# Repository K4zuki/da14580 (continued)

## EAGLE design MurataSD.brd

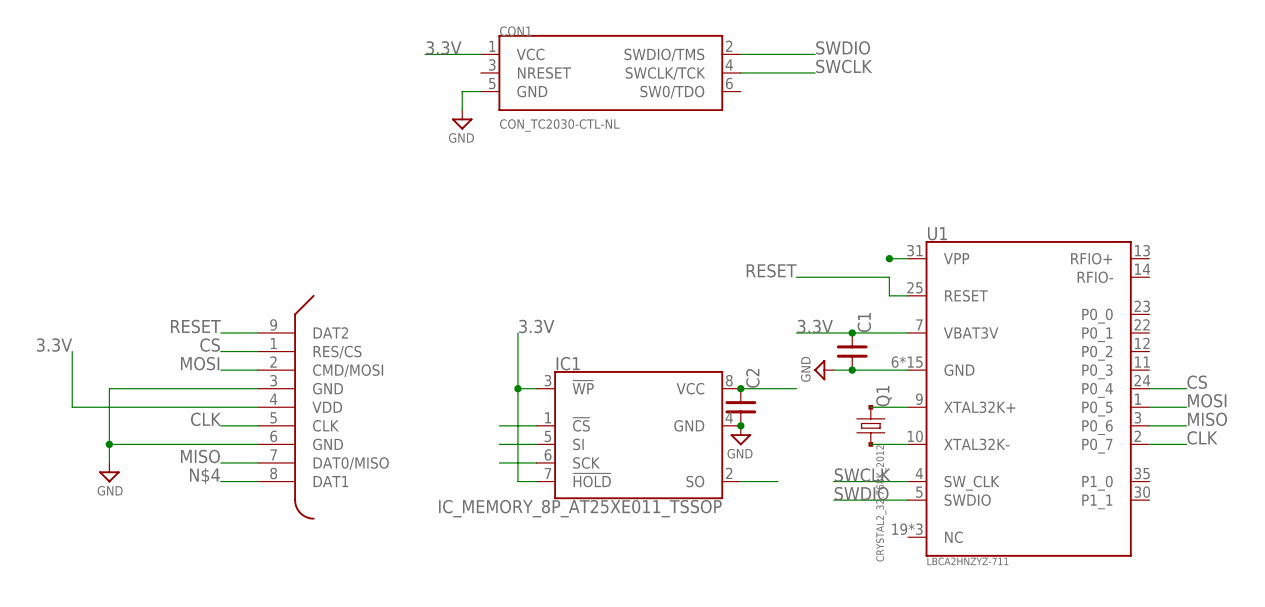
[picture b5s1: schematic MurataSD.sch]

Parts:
C1, C2: C_SMD_0.1U_1005; C0402
CON1: CON_TC2030-CTL-NL; CON_TC2030-IDC-NL
IC1: IC_MEMORY_8P_AT25XE011_TSSOP; IC_08_0.65_160MIL
Q1: CRYSTAL2_32.768K_2012; CR_2125
U1: LBCA2HNZYZ-711; IC_MURATA_LBCA2HNZYZ-711
U2: BOARD_MMC

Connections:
3.3V: C1.1, C2.1, CON1.1 (VCC), IC1.3 (!WP), IC1.7 (!HOLD), IC1.8 (VCC), U1.7 (VBAT3V), U2.4 (VDD)
CLK: IC1.6 (SCK), U1.2 (P0_7), U2.5 (CLK)
CS: IC1.1 (!CS), U1.24 (P0_4), U2.1 (RES/CS)
GND: C1.2, C2.2, CON1.5 (GND), IC1.4 (GND), U1.6 (GND), U1.8 (GND), U1.15 (GND), U1.16 (GND), U1.17 (GND), U1.18 (GND), U1.20 (GND), U1.21 (GND), U1.26 (GND), U1.27 (GND), U1.28 (GND), U1.29 (GND), U1.32 (GND), U1.33 (GND), U1.34 (GND), U2.3 (GND), U2.6 (GND)
MISO: IC1.2 (SO), U1.3 (P0_6), U2.7 (DAT0/MISO)
MOSI: IC1.5 (SI), U1.1 (P0_5), U2.2 (CMD/MOSI)
unnamed: Q1.1, U1.9 (XTAL32K+)
unnamed: Q1.2, U1.10 (XTAL32K-)
RESET: U1.25 (RESET), U2.9 (DAT2)
SWCLK: CON1.4 (SWCLK/TCK), U1.4 (SW_CLK)
SWDIO: CON1.2 (SWDIO/TMS), U1.5 (SWDIO)

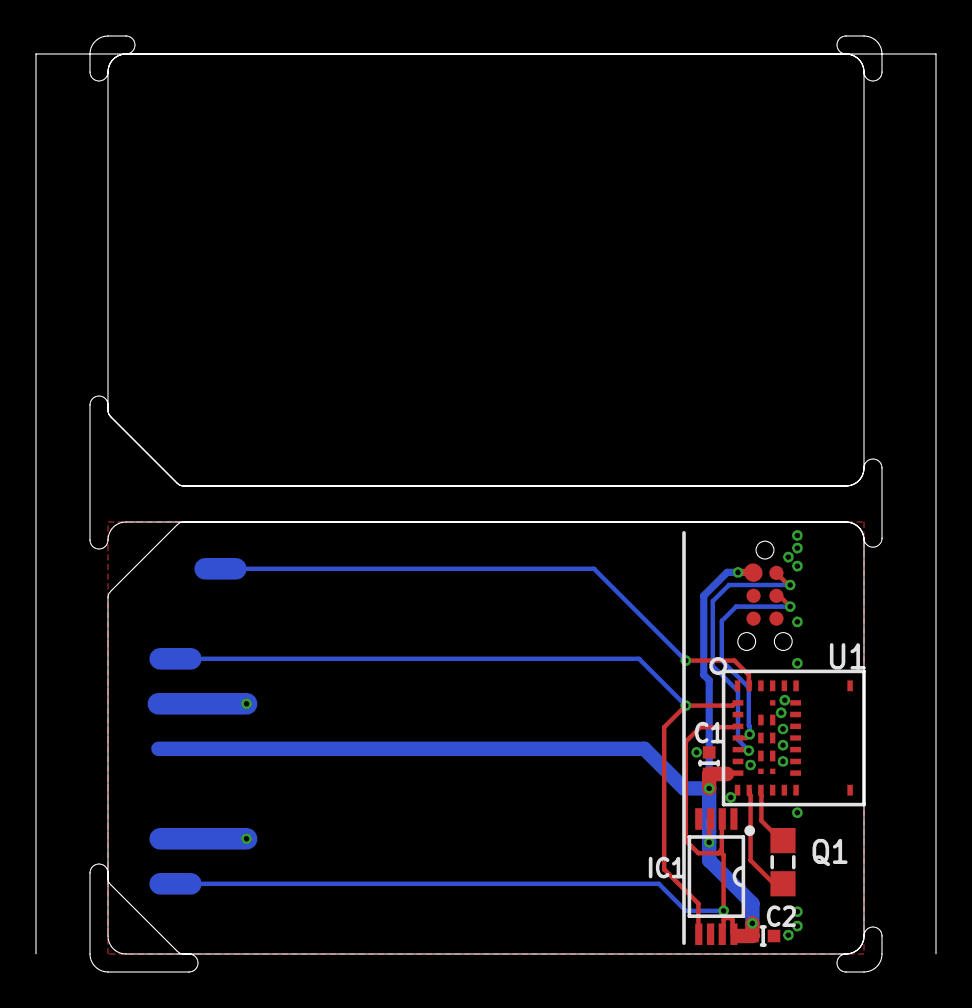
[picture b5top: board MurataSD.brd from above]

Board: 2 copper layers, 44.0 x 52.0 mm, 7 parts (0 on the bottom side), 11 nets.

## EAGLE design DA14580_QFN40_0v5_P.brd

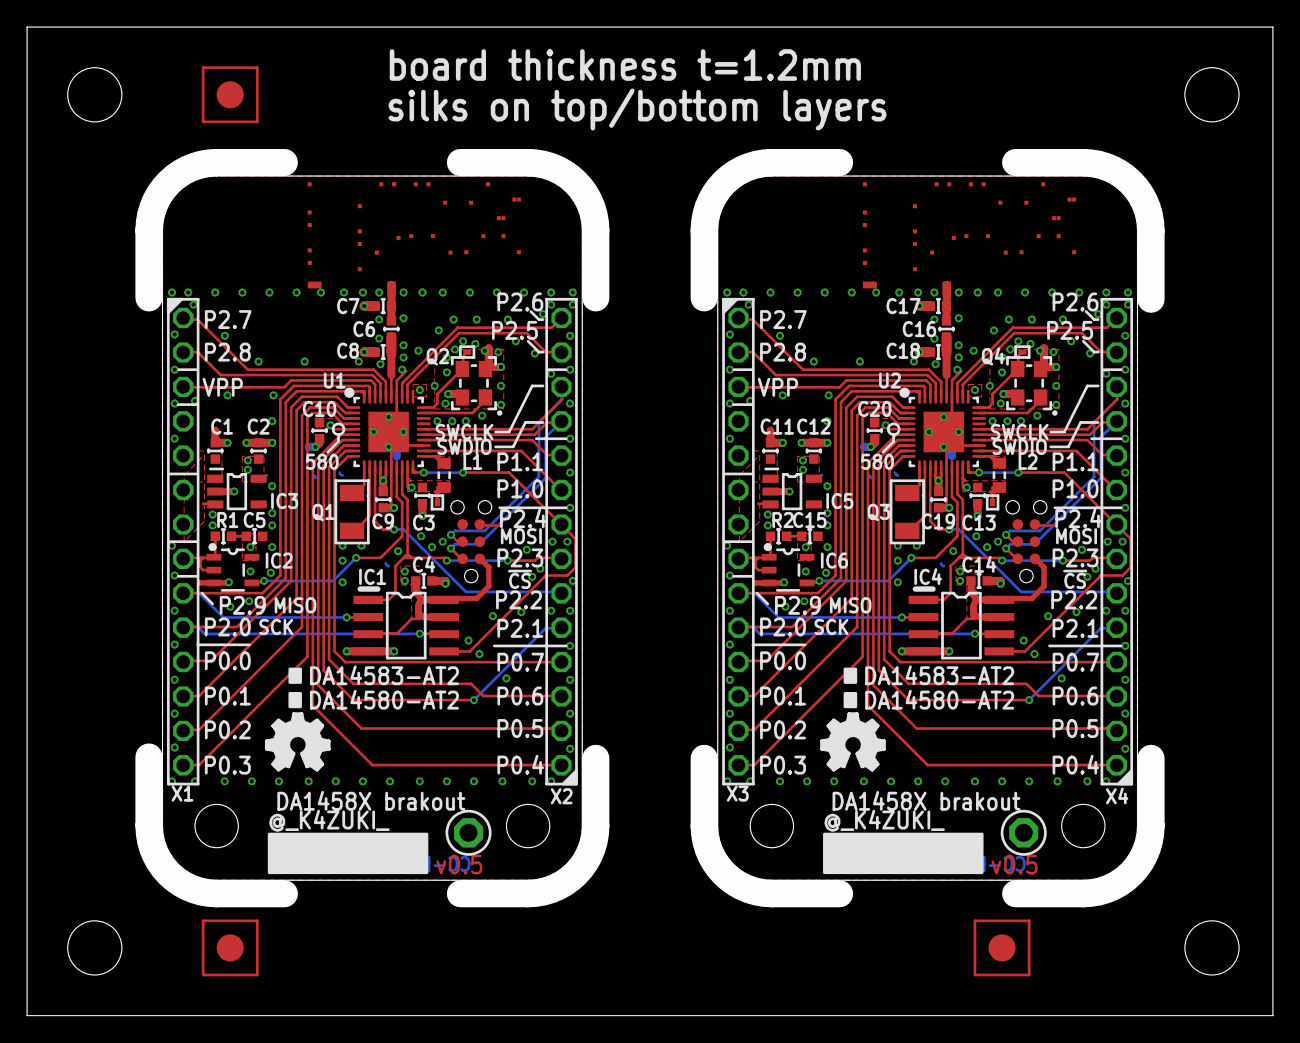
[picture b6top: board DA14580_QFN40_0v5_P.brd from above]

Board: 2 copper layers, 92.0 x 73.0 mm, 55 parts (0 on the bottom side), 70 nets.

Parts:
C1, C2, C3, C4, C5, C9, C10, C11, C12, C13, C14, C15, C19, C20: C0402
C6, C7, C8, C16, C17, C18: NM; C0402
CON1, CON2: CON_TC2030-CTL-NL; CON_TC2030-IDC-NL
IC1, IC4: IC_MEMORY_8P_AT25XE011_SOP; IC_08_1.27_150MIL
IC2, IC6: NC7SZ00M5XCT-ND; SOT23-5
IC3, IC5: LDO5_3.3_SOT23; IC_05_0.95_50MIL
L1, L2: L_1608
Q1, Q3: 32.768k; CRYSTAL_FC-135
Q2, Q4: 16M/2520; CLOCK_2520
R1, R2: C0402
TP1, TP2, TP5, TP6: TESTPAD; TP06RECT
TP3, TP4: TPPAD1-13; P1-13
TP91, TP92, TP93: TESTPAD_F; FIDUCIAL
U1, U2: DA14583AT2; QFN40_0.4P5.0X5.0
U$1, U$3: ANT_IFA; ANT_IFA_V2
U$2, U$4: ICON_OSHW
X1, X2, X3, X4: SSW-114-02-S-S

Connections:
!RESET!: IC2.1, IC2.2, R1.1, X1.8
!RESET!1: IC6.1, IC6.2, R2.1, X3.8
GND: C1.2, C2.2, C3.2, C4.2, C5.2, C6.2, C7.1, C7.2, C8.2, C9.2, C10.2, CON1.5, IC1.4, IC2.3, IC3.2, Q2.2, Q2.4, TP3.TP, U1.16, U1.23, U1.34, U1.BP, U$1.ANT, U$1.GND, U$1.GND@1, U$1.GND@2, U$1.GND@3, U$1.GND@4, U$1.GND@5, U$1.GND@6, U$1.GND@7, U$1.GND@8, U$1.GND@9, U$1.GND@10, U$1.GND@11, U$1.GND@12, U$1.GND@13, U$1.GND@14, U$1.GND@15, U$1.GND@16, U$1.GND@17, U$1.GND@18, U$1.GND@19, U$1.GND@20, U$1.GND@21, U$1.GND@22, U$1.GND@23, U$1.GND@24, U$1.GND@25, U$1.GND@26, U$1.GND@27, U$1.GND@28, U$1.GND@29, U$1.GND@30, X1.4, X1.5
GND1: C11.2, C12.2, C13.2, C14.2, C15.2, C16.2, C17.1, C17.2, C18.2, C19.2, C20.2, CON2.5, IC4.4, IC5.2, IC6.3, Q4.2, Q4.4, TP4.TP, U2.16, U2.23, U2.34, U2.BP, U$3.ANT, U$3.GND, U$3.GND@1, U$3.GND@2, U$3.GND@3, U$3.GND@4, U$3.GND@5, U$3.GND@6, U$3.GND@7, U$3.GND@8, U$3.GND@9, U$3.GND@10, U$3.GND@11, U$3.GND@12, U$3.GND@13, U$3.GND@14, U$3.GND@15, U$3.GND@16, U$3.GND@17, U$3.GND@18, U$3.GND@19, U$3.GND@20, U$3.GND@21, U$3.GND@22, U$3.GND@23, U$3.GND@24, U$3.GND@25, U$3.GND@26, U$3.GND@27, U$3.GND@28, U$3.GND@29, U$3.GND@30, X3.4, X3.5
unnamed: C6.1, C8.1, U1.35
unnamed: Q3.1, U2.12
unnamed: Q3.2, U2.11
unnamed: Q4.1, U2.29
unnamed: Q4.3, TP6.TP, U2.30
unnamed: L1.2, U1.21
unnamed: L2.2, U2.21
unnamed: C13.1, L2.1, TP5.TP, U2.19, U2.31
unnamed: C3.1, L1.1, TP1.TP, U1.19, U1.31
unnamed: C16.1, C18.1, U2.35
unnamed: Q1.1, U1.12
unnamed: Q1.2, U1.11
unnamed: Q2.1, U1.29
unnamed: Q2.3, TP2.TP, U1.30
P0_0: U1.1, X1.11
P0_1: U1.2, X1.12
P0_2: U1.3, X1.13
P0_3: U1.4, X1.14
P0_4: U1.6, X2.1
P0_5: U1.7, X2.2
P0_6: U1.9, X2.3
P0_7: U1.10, X2.4
P0_8: U2.1, X3.11
P0_9: U2.2, X3.12
P0_10: U2.3, X3.13
P0_11: U2.4, X3.14
P0_12: U2.7, X4.2
P0_13: U2.6, X4.1
P0_14: U2.10, X4.4
P0_15: U2.9, X4.3
P1_0: U1.22, X2.9
P1_1: U1.24, X2.10
P1_4: U2.22, X4.9
P1_5: U2.24, X4.10
P2_0: IC1.6, U1.40, X1.10
P2_1: U1.8, X2.5
P2_2: U1.13, X2.6
P2_3: IC1.1, U1.18, X2.7
P2_4: IC1.5, U1.20, X2.8
P2_5: U1.32, X2.13
P2_6: U1.33, X2.14
P2_7: U1.36, X1.1
P2_8: U1.37, X1.2
P2_9: IC1.2, U1.39, X1.9
P2_10: IC4.1, U2.18, X4.7
P2_11: U2.13, X4.6
P2_12: IC4.6, U2.40, X3.10
P2_13: U2.8, X4.5
P2_14: U2.32, X4.13
P2_15: U2.33, X4.14
P2_16: IC4.2, U2.39, X3.9
P2_17: IC4.5, U2.20, X4.8
P2_18: U2.36, X3.1
P2_19: U2.37, X3.2
RESET: IC2.4, U1.17
RESET1: IC6.4, U2.17
SWCLK: CON1.4, U1.26, X2.12
SWCLK1: CON2.4, U2.26, X4.12
SWDIO: CON1.2, U1.25, X2.11
SWDIO1: CON2.2, U2.25, X4.11
VCC: C2.1, C4.1, C5.1, C9.1, C10.1, CON1.1, IC1.3, IC1.7, IC1.8, IC2.5, IC3.5, R1.2, U1.5, U1.14, U1.15
VCC1: C12.1, C14.1, C15.1, C19.1, C20.1, CON2.1, IC4.3, IC4.7, IC4.8, IC5.5, IC6.5, R2.2, U2.5, U2.14, U2.15
VDD: C1.1, IC3.1, IC3.3, X1.6, X1.7
VDD1: C11.1, IC5.1, IC5.3, X3.6, X3.7
VPP: U1.38, X1.3
VPP1: U2.38, X3.3

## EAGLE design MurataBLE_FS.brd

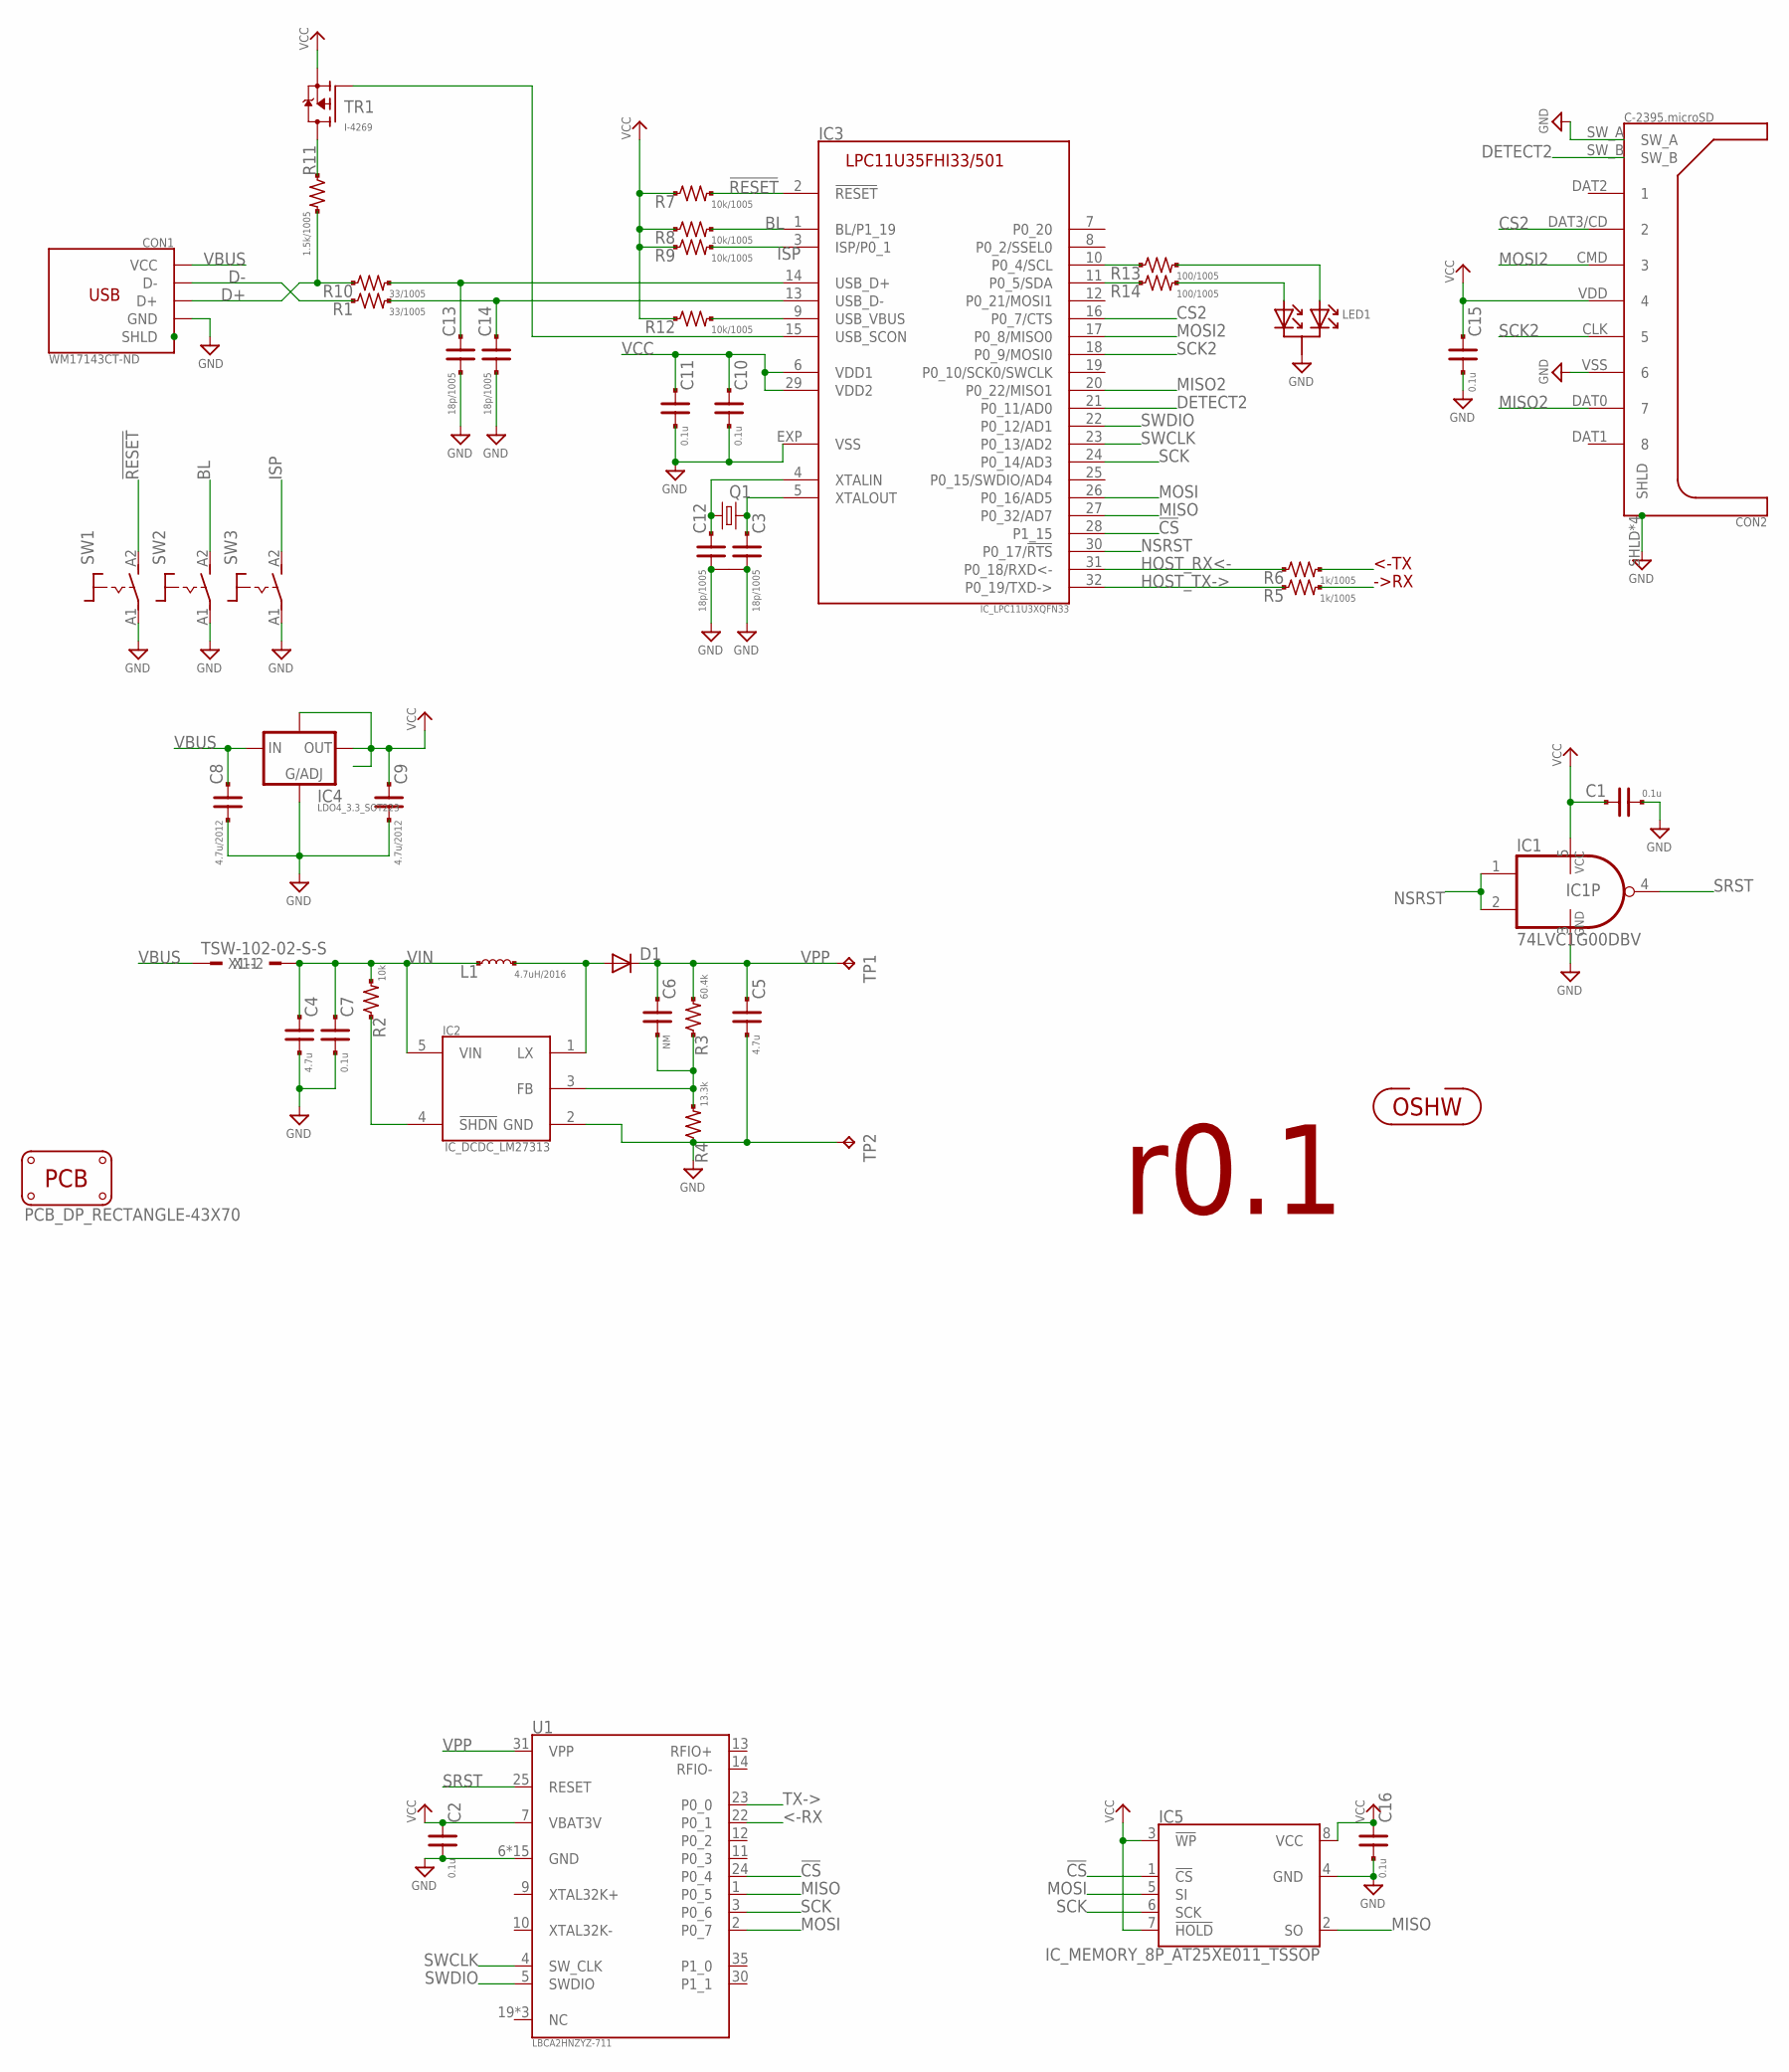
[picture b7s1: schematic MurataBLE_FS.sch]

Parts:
C1, C2, C10, C11, C16: 0.1u; C0402
C3, C12, C13, C14: 18p/1005; C0402
C4, C5: 4.7u; CR_2125
C6: NM; CR_1608
C7, C15: 0.1u; CR_1608
C8, C9: 4.7u/2012; CR_2125
CON1: WM17143CT-ND; CON_USB_47589-0001MOLEX
CON2: C-2395.microSD; CON_MICROSD_C2395
D1: DIODE_SMALL; DIODE_2125
IC1: 74LVC1G00DBV; SOT23-5
IC2: IC_DCDC_LM27313; IC_05_0.95_50MIL
IC3: IC_LPC11U3XQFN33; HVQFN33
IC4: LDO4_3.3_SOT223; IC_SOT223
IC5: IC_MEMORY_8P_AT25XE011_TSSOP; IC_08_0.65_160MIL
L1: 4.7uH/2016; L_2016
LED1: LED_1SEG_A2K1; SOT95P300X140-3N
PCB1: PCB_DP_RECTANGLE-43X70; DP7043_V1
Q1: CRYSTAL4_12M_3225; CLOCK_3225
R1, R10: 33/1005; C0402
R2: 10k; R_1608_PADPAD
R3: 60.4k; R_1608_PADPAD
R4: 13.3k; R_1608_PADPAD
R5, R6: 1k/1005; C0402
R7, R8, R9, R12: 10k/1005; C0402
R11: 1.5k/1005; C0402
R13, R14: 100/1005; C0402
SW1, SW3: TACTSW2_BK_P807X; SW_TACTSW_P8073
SW2: TACTSW2_WH_P807X; SW_TACTSW_P8073
TP1: P7592; P1-13
TP2: P7591; P1-13
TR1: I-4269; SOT95P300X140-3N
U1: LBCA2HNZYZ-711; IC_MURATA_LBCA2HNZYZ-711
U$1: ICON_OSHW
X1: TSW-102-02-S-S

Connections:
!CS!: IC3.28 (P1_15), IC5.1 (!CS), U1.24 (P0_4)
!RESET!: IC3.2 (!RESET!), R7.2, SW1.A2 (S)
<-RX: R5.2, U1.22 (P0_1)
BL: IC3.1 (BL/P1_19), R8.2, SW2.A2 (S)
CS2: CON2.DAT3/CD (2), IC3.16 (P0_7/CTS)
D+: CON1.3 (D+), R10.1, R11.2
D-: CON1.2 (D-), R1.1
DETECT2: CON2.SW_B, IC3.21 (P0_11/AD0)
GND: C1.2, C2.2, C3.2, C4.2, C5.2, C7.2, C8.2, C9.2, C10.2, C11.2, C12.2, C13.2, C14.2, C15.2, C16.2, CON1.5 (GND), CON2.SHLD, CON2.SHLD@2 (SHLD), CON2.SHLD@3 (SHLD), CON2.SHLD@4 (SHLD), CON2.SW_A, CON2.VSS (6), IC1.3 (GND), IC2.2 (GND), IC3.EXP (VSS), IC4.1 (ADJ), IC5.4 (GND), LED1.3 (K1), Q1.2, Q1.4, R4.1, SW1.A1, SW2.A1, SW3.A1, TP2.TP, U1.6 (GND), U1.8 (GND), U1.15 (GND), U1.16 (GND), U1.17 (GND), U1.18 (GND), U1.20 (GND), U1.21 (GND), U1.26 (GND), U1.27 (GND), U1.28 (GND), U1.29 (GND), U1.32 (GND), U1.33 (GND), U1.34 (GND)
HOST_RX<-: IC3.31 (P0_18/RXD<-), R6.1
HOST_TX->: IC3.32 (P0_19/TXD->), R5.1
ISP: IC3.3 (ISP/P0_1), R9.2, SW3.A2 (S)
MISO: IC3.27 (P0_32/AD7), IC5.2 (SO), U1.1 (P0_5)
MISO2: CON2.DAT0 (7), IC3.20 (P0_22/MISO1)
MOSI: IC3.26 (P0_16/AD5), IC5.5 (SI), U1.2 (P0_7)
MOSI2: CON2.CMD (3), IC3.17 (P0_8/MISO0)
unnamed: R11.1, TR1.3 (D)
unnamed: IC3.10 (P0_4/SCL), R13.1
unnamed: CON1.SHD (SHLD), CON1.SHD$1 (SHLD), CON1.SHD$2 (SHLD), CON1.SHD$3 (SHLD), CON1.SHD$4 (SHLD), CON1.SHD$5 (SHLD), CON1.SHD$6 (SHLD), CON1.SHD$7 (SHLD)
unnamed: C12.1, IC3.4 (XTALIN), Q1.1
unnamed: IC3.11 (P0_5/SDA), R14.1
unnamed: D1.A, IC2.1 (LX), L1.2
unnamed: IC2.4 (!SHDN!), R2.1
unnamed: LED1.2 (A2), R13.2
unnamed: C6.2, IC2.3 (FB), R3.1, R4.2
unnamed: C3.1, IC3.5 (XTALOUT), Q1.3 (2)
unnamed: IC3.15 (USB_SCON), TR1.1 (G)
unnamed: IC3.9 (USB_VBUS), R12.2
unnamed: LED1.1 (A1), R14.2
unnamed: C13.1, IC3.14 (USB_D+), R10.2
unnamed: C14.1, IC3.13 (USB_D-), R1.2
NSRST: IC1.1 (I0), IC1.2 (I1), IC3.30 (P0_17/!RTS!)
SCK: IC3.24 (P0_14/AD3), IC5.6 (SCK), U1.3 (P0_6)
SCK2: CON2.CLK (5), IC3.18 (P0_9/MOSI0)
SRST: IC1.4 (O), U1.25 (RESET)
SWCLK: IC3.23 (P0_13/AD2), U1.4 (SW_CLK)
SWDIO: IC3.22 (P0_12/AD1), U1.5 (SWDIO)
TX->: R6.2, U1.23 (P0_0)
VBUS: C8.1, CON1.1 (VCC), IC4.3 (IN), X1.1
VCC: C1.1, C2.1, C9.1, C10.1, C11.1, C15.1, C16.1, CON2.VDD (4), IC1.5 (VCC), IC3.6 (VDD1), IC3.29 (VDD2), IC4.2 (OUT), IC4.4 (OUT/EN/NC), IC5.3 (!WP), IC5.7 (!HOLD), IC5.8 (VCC), R7.1, R8.1, R9.1, R12.1, TR1.2 (S), U1.7 (VBAT3V)
VIN: C4.1, C7.1, IC2.5 (VIN), L1.1, R2.2, X1.2
VPP: C5.1, C6.1, D1.K (C), R3.2, TP1.TP, U1.31 (VPP)

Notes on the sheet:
r0.1
->RX
<-TX

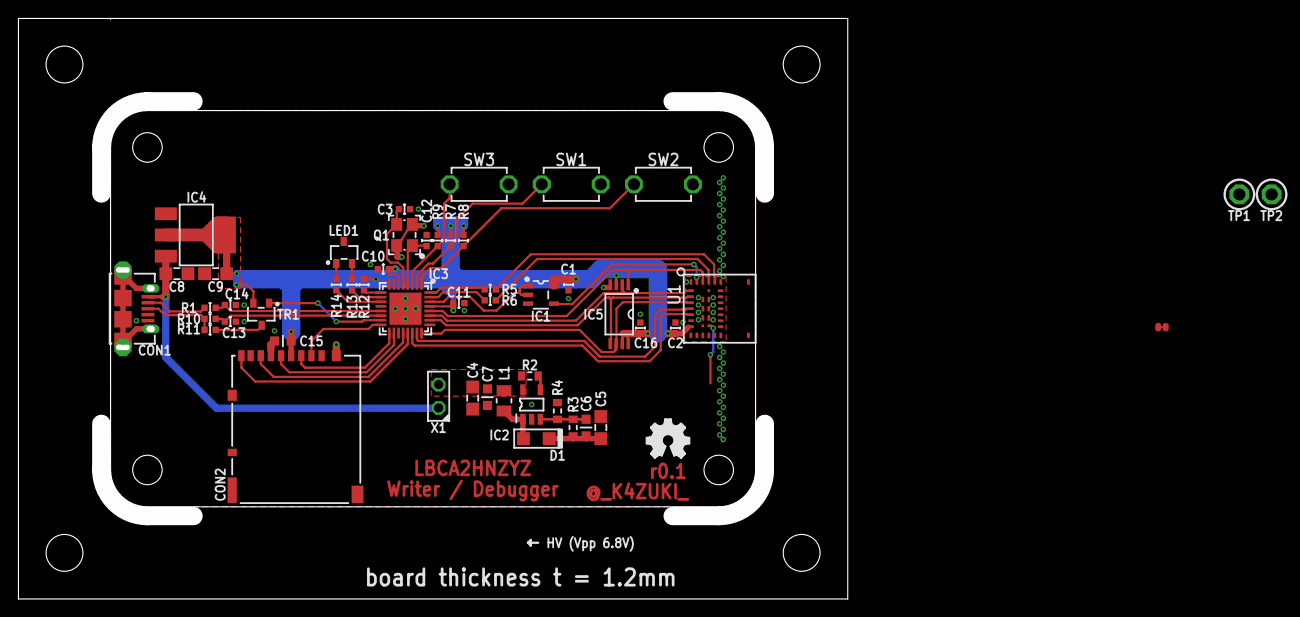
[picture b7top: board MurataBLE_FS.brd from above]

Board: 2 copper layers, 90.0 x 63.0 mm, 51 parts (0 on the bottom side), 42 nets.

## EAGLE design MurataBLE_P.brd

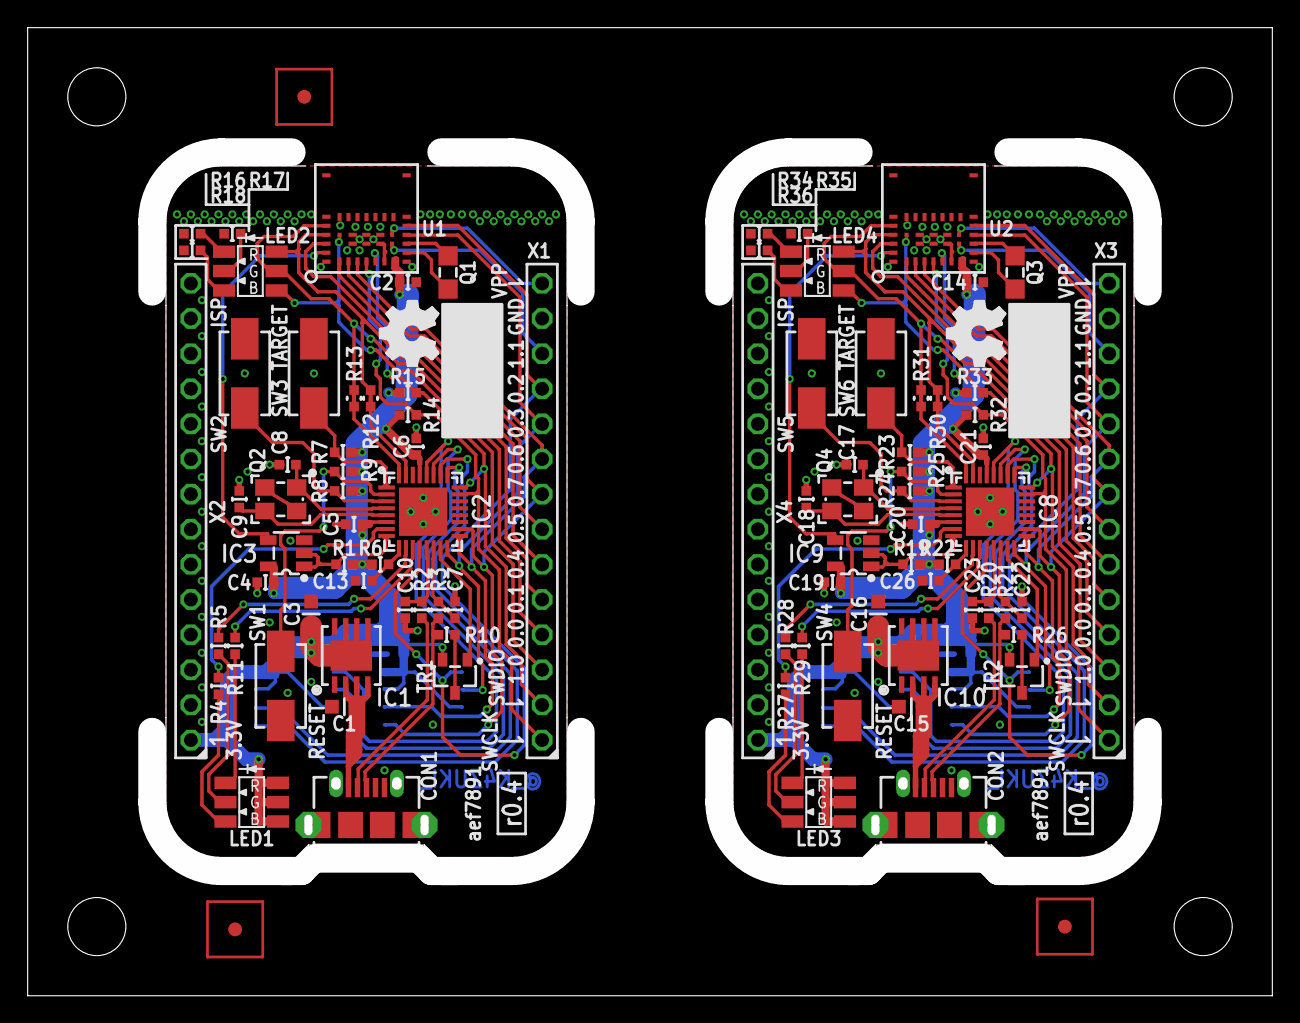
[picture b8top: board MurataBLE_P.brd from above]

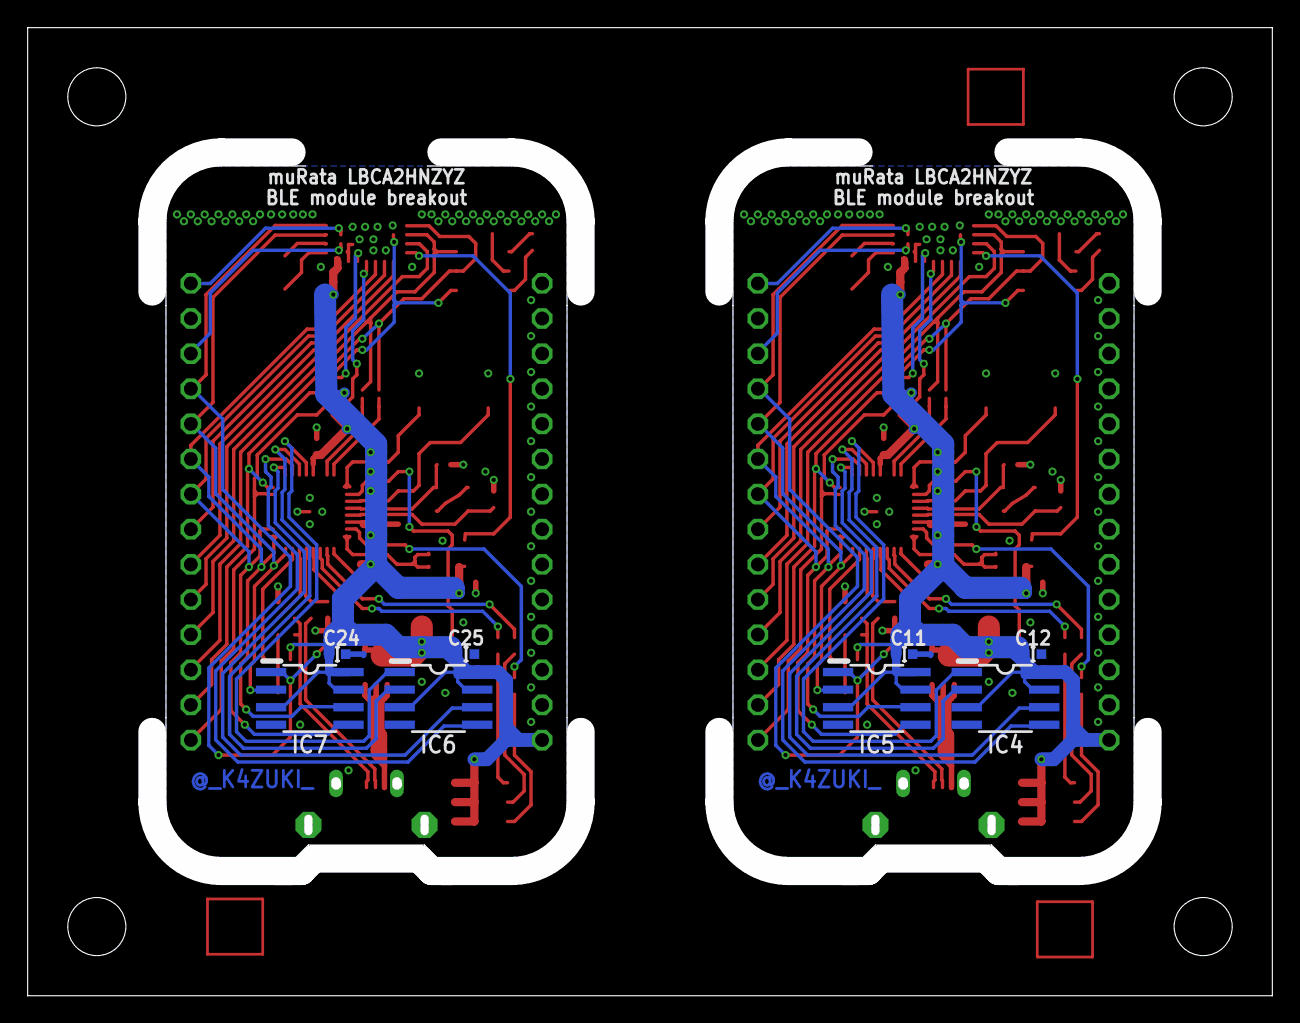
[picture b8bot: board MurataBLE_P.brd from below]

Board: 2 copper layers, 90.0 x 70.0 mm, 113 parts (8 on the bottom side), 94 nets.

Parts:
C1, C3, C15, C16: 1u/1608; CR_1608
C2, C4, C5, C6, C11, C12, C13, C14, C19, C20, C21, C24, C25, C26: 0.1u/1005; C0402
C7, C8, C9, C10, C17, C18, C22, C23: 18p/1005; C0402
CON1, CON2: 47589-0001; CON_USB_47589-0001MOLEX
GIT1, GIT2: aef7891; GIT-REVISION
IC1, IC10: DFN80P410X410_8N
IC2, IC8: LPC11U35_QFN33; HVQFN33
IC3, IC9: NC7SZ00; SOT95P280X145-5N
IC4, IC6: AT25DN512C; IC_08_1.27_150MIL
IC5, IC7: AT25XE011; IC_08_1.27_150MIL
ICON1, ICON3: r0.4; ICON_REVISION1.2
ICON2, ICON4: NC; ICON_OSHW
LED1, LED2, LED3, LED4: LED_3SEG; LED_3SEG_SMD
P1, P2, P3, P4, P5, P6, P7, P8: NC; PCB_CORNER_NH
Q1, Q3: 32.768K/2012; CR_2125
Q2, Q4: 12M/3225; CLOCK_3225
R1, R6, R7, R8, R9, R14, R15, R19, R22, R23, R24, R25, R32, R33: 10k/1005; C0402
R2, R3, R20, R21: 33/1005; C0402
R4, R5, R11, R16, R17, R18, R27, R28, R29, R34, R35, R36: 1k/1005; C0402
R10, R26: 1.5k/1005; C0402
R12, R13, R30, R31: NC; R0402SHORT
SW1, SW2, SW3, SW4, SW5, SW6: FSM2JMTR; SW_TACTSW_FSM2JMTR
TP100, TP101, TP102: NC; FIDUCIAL
TR1, TR2: BSS84; SOT95P300X140-3N
U1, U2: LBCA2HNZYZ; IC_MURATA_LBCA2HNZYZ-711
X1, X2, X3, X4: TSW-114-02-S-S; TSW-114-07-F-S

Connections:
3.3V: C2.1, C3.1, C4.1, C5.1, C6.1, C11.1, C12.1, IC1.5, IC1.6, IC1.7, IC1.EP, IC2.6, IC2.29, IC3.5, IC4.3, IC4.7, IC4.8, IC5.3, IC5.7, IC5.8, LED1.4, LED1.5, LED1.6, R1.1, R6.1, R7.1, R8.1, R9.1, R14.2, R15.2, TR1.2, U1.7, X2.1
3.3V1: C14.1, C16.1, C19.1, C20.1, C21.1, C24.1, C25.1, IC6.3, IC6.7, IC6.8, IC7.3, IC7.7, IC7.8, IC8.6, IC8.29, IC9.5, IC10.5, IC10.6, IC10.7, IC10.EP, LED3.4, LED3.5, LED3.6, R19.1, R22.1, R23.1, R24.1, R25.1, R32.2, R33.2, TR2.2, U2.7, X4.1
580.P0_0: LED2.4, R12.3, U1.23, X1.5
580.P0_1: LED2.5, R13.3, U1.22, X1.4
580.P0_2: IC2.12, IC5.1, U1.12, X1.11
580.P0_3: IC2.16, IC5.2, U1.11, X1.10
580.P0_4: U1.24, X1.6
580.P0_5: U1.1, X1.7
580.P0_6: IC2.17, IC5.6, U1.3, X1.9
580.P0_7: IC2.18, IC5.5, U1.2, X1.8
580.P0_8: U2.1, X3.7
580.P0_9: IC7.6, IC8.17, U2.3, X3.9
580.P0_10: IC7.5, IC8.18, U2.2, X3.8
580.P0_11: IC7.1, IC8.12, U2.12, X3.11
580.P0_12: IC7.2, IC8.16, U2.11, X3.10
580.P0_13: U2.24, X3.6
580.P0_14: LED4.4, R30.3, U2.23, X3.5
580.P0_15: LED4.5, R31.3, U2.22, X3.4
580.P1_0: LED2.6, U1.35, X1.3
580.P1_1: U1.30, X1.12
580.P1_2: LED4.6, U2.35, X3.3
580.P1_3: U2.30, X3.12
!RESET!: IC2.2, R9.2, SW1.2
!RESET!1: IC8.2, R25.2, SW4.2
FB_BL: IC2.1, R7.2, SW3.2
FB_BL1: IC8.1, R23.2, SW6.2
FB_ISP: IC2.3, R8.2, SW2.2
FB_ISP1: IC8.3, R24.2, SW5.2
GND: C1.2, C2.2, C3.2, C4.2, C5.2, C6.2, C7.2, C8.2, C9.2, C10.2, C11.2, C12.2, C13.2, CON1.5, CON1.SHD, CON1.SHD$1, CON1.SHD$2, CON1.SHD$3, CON1.SHD$4, CON1.SHD$5, CON1.SHD$6, CON1.SHD$7, IC1.1, IC2.EXP, IC3.3, IC4.4, IC5.4, Q2.2, Q2.4, R16.2, R17.2, R18.2, SW1.1, SW2.1, SW3.1, U1.6, U1.8, U1.15, U1.16, U1.17, U1.18, U1.20, U1.21, U1.26, U1.27, U1.28, U1.29, U1.32, U1.33, U1.34, X1.13
GND1: C14.2, C15.2, C16.2, C17.2, C18.2, C19.2, C20.2, C21.2, C22.2, C23.2, C24.2, C25.2, C26.2, CON2.5, CON2.SHD, CON2.SHD$1, CON2.SHD$2, CON2.SHD$3, CON2.SHD$4, CON2.SHD$5, CON2.SHD$6, CON2.SHD$7, IC6.4, IC7.4, IC8.EXP, IC9.3, IC10.1, Q4.2, Q4.4, R34.2, R35.2, R36.2, SW4.1, SW5.1, SW6.1, U2.6, U2.8, U2.15, U2.16, U2.17, U2.18, U2.20, U2.21, U2.26, U2.27, U2.28, U2.29, U2.32, U2.33, U2.34, X3.13
unnamed: Q1.1, U1.9
unnamed: Q1.2, U1.10
unnamed: C13.1, IC2.9, R6.2
unnamed: Q3.1, U2.9
unnamed: R10.1, TR1.3
unnamed: IC2.15, TR1.1
unnamed: IC2.7, R4.1
unnamed: IC2.10, R5.1
unnamed: IC2.11, R11.1
unnamed: LED1.1, R11.2
unnamed: LED1.2, R5.2
unnamed: LED1.3, R4.2
unnamed: LED2.3, R18.1
unnamed: LED2.2, R17.1
unnamed: LED2.1, R16.1
unnamed: Q3.2, U2.10
unnamed: C8.1, IC2.4, Q2.1
unnamed: C9.1, IC2.5, Q2.3
unnamed: C7.1, IC2.14, R3.2
unnamed: CON1.3, R3.1, R10.2
unnamed: CON1.2, R2.1
unnamed: C17.1, IC8.4, Q4.1
unnamed: C10.1, IC2.13, R2.2
unnamed: C18.1, IC8.5, Q4.3
unnamed: CON2.3, R21.1, R26.2
unnamed: CON2.2, R20.1
unnamed: C22.1, IC8.14, R21.2
unnamed: C23.1, IC8.13, R20.2
unnamed: C26.1, IC8.9, R22.2
unnamed: R26.1, TR2.3
unnamed: IC8.15, TR2.1
unnamed: IC8.7, R27.1
unnamed: IC8.10, R28.1
unnamed: IC8.11, R29.1
unnamed: LED3.2, R28.2
unnamed: LED3.1, R29.2
unnamed: LED3.3, R27.2
unnamed: LED4.3, R36.1
unnamed: LED4.2, R35.1
unnamed: LED4.1, R34.1
NSRST: IC2.8, IC3.1, IC3.2, R1.2
NSRST1: IC8.8, IC9.1, IC9.2, R19.2
P0_1: IC6.2, IC8.27
P0_2: IC6.5, IC8.26
P0_3: IC6.6, IC8.25
P0_15: IC2.25, IC4.6
P0_16: IC2.26, IC4.5
P0_32: IC2.27, IC4.2
P1_1: IC6.1, IC8.28
P1_15: IC2.28, IC4.1
RESET: IC3.4, U1.25
RESET1: IC9.4, U2.25
SWCLK: IC2.23, R14.1, U1.4, X1.1
SWCLK1: IC8.23, R32.1, U2.4, X3.1
SWDIO: IC2.24, R15.1, U1.5, X1.2
SWDIO1: IC8.24, R33.1, U2.5, X3.2
TGT_RX: IC2.32, R13.1, R13.2
TGT_RX1: IC8.32, R31.1, R31.2
TGT_TX: IC2.31, R12.1, R12.2
TGT_TX1: IC8.31, R30.1, R30.2
VPP: U1.31, X1.14
VPP2: U2.31, X3.14
VUSB: C1.1, CON1.1, IC1.2, IC1.3, IC1.4
VUSB1: C15.1, CON2.1, IC10.2, IC10.3, IC10.4

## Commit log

2015-03-02 [ NEW ] MurataBLE
    Murata LBCA2HNZYZ-711 module evaluation board
2015-03-02 [ FIX ] GND plane
2015-03-02 [ NEW ] Gerbers
2015-03-02 .gitignore
2015-03-02 [ NEW ] gerbv file
2015-03-02 [ BRD ] silk placement change
    Silk moved to north; related gerber change
2015-03-02 [ NEW ] MurataSD
2015-03-03 [ BRD ] removed panel frame
2015-03-03 [ NEW ] BOARD_MMC
2015-03-04 [ FIX ] BOARD_MMC update
2015-03-04 schematic update
2015-03-06 update silk
2015-03-06 [ FIX ] library update
2015-03-09 [ NEW ] MurataMicroSD IC_MURATA_LBCA2HNZYZ-711 on extended microSD card size PCB
2015-03-09 gitignore
2015-03-09 [ NEW ] Gerbers(MurataMicroSD) Gerber files and gerbv file
2015-03-09 [ NEW ] MurataMicroSD_P panelised version of MurataMicroSD.brd no schematic file
2015-03-09 design rule file for MurataMicroSD_P
2015-03-09 [ FIX ] GML/milling layer removed dimention layer in original file
2015-03-09 [ FIX ] milling layer
2015-03-10 [ FIX ] MurataMicroSD
    add via for GND
2015-03-11 [ FIX ] SCH change; library update myPCBlib: 385519d7d8f28a1be9991780ecc3cf499a6be8e2
2015-03-11 [ FIX ] library update; trace; increase via myPCBlib: 0aa2107fd28665ba7552473a3fbc4a367f8d93bf
2015-03-12 [ FIX ] MurataMicroSD
    airwire removed; tiny trace change
2015-03-12 [ FIX ] MurataBLE
    small schema change
    library update
    increase GND via
    C2 moved
2015-03-12 [ FIX ] fix trace, increase via
2015-03-12 [ FIX ] BLE module placed on top
    other side of uSD contacts
2015-03-12 [ uSD ] library update; inrease via; silk and bottom trace board name on top silk name and revision on bottom trace
2015-03-12 [ uSD ][ GERBER ] panelise as update
2015-03-16 [ uSD_P ] extend outline
    PCBCART does not accept V-cut in outline below 55x55mm.
    extended to 60x60 plus add 2x V-cut lines
2015-03-16 [ USB ][ FIX ] values of each components; replace PMOS to SOT23 package - R/C's value updated - replace to use SOT23 package MOS
2015-03-16 [ USB ][ FIX ] Dimention; PMOS replace; silk on pinheader; via - demention changed to 60x55mm, vcut and milling added - PMOS replaced as schematic update - silk added on X1 pin header - via slight mo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
2015-03-16 [ uSD ][ FIX ] extend board size to 60x60
2015-03-17 [ USB ][ FIX ] library update
2015-03-17 [ USB ] moved 2mm north; bigger milling; add silk
2015-03-18 [ USB ] Q1 replace to CRYSTAL_FC-135
2015-03-18 [ USB ] schematic tiny change
2015-03-18 [ FIX ] CLOCK_CRYSTAL;library update; part value
2015-03-18 [ FIX ] texts
2015-03-24 [ uSD ] fix as per library
2015-03-30 [ FIX ][ USB ] milling layer
2015-03-30 [USB]
2015-03-30 [ FIX ][ USB ] Merge
2015-03-30 [ uSD ] library update mylib.lbr: 324fe0c1e5958541035a4848493b76da56c91cd1
2015-03-30 [ uSD ] fix
2015-03-31 [ uSD ] dimention lines
    moved dimention lines to avoid finished dimention size error after V-cut
2015-03-31 [ USB ] panelized
2015-03-31 [ uSD ] revision 3
2015-03-31 [ USB ] fix
2015-04-07 [ uSD ] P0_1 on testpad
2015-04-08 [ USB ] R6 moved
2015-04-08 [ USB ] increase outline margin
2015-04-08 [ USB ] indicator LED added
2015-04-09 [ USB ][ FIX ] move R11 and Vdd
2015-04-09 [ USB ][ FIX ] resistor value
2015-04-09 [ FIX ] fixes as per update of mylib/LED_3SEG
2015-04-12 [ uSD ][ SCH ] center-left
2015-04-13 [ USB ] trace fix
2015-04-13 [ USB ] trace fix
    VDD trace
2015-04-14 [ USB ][ BRD ] IC1,C1,C3 moved
2015-04-15 [ USB ][ FIX ] USB connection
    Fix USB line connection over R2,3,10, C7,10 and TR1
    referenced to AN11392,NXP
2015-04-15 [ USB ][ BRD ] FIX
2015-04-16 update LICENSE
2015-04-16 rename LOCENSE to LOCENSE.md
2015-04-16 [ USB ] lisence stated
    CC-BY-SA
2015-04-16 [ USB ] extend pin header X1
    now ALL pins on header
2015-04-16 [ USB ] update as library
    TP
    X1 Pin header
2015-04-16 [ USB ][ BRD ] add jumpers
    added jumpers to keep net name on schematic
2015-04-17 [ uSD ] panel outline/ P1_0/1 on pad
    - extend panel size
    - add 2.2mm drill
    - all but 32k xtal to be on pad
    - pads on top and bottom
2015-04-17 [ uSD ][ FIX ] license stated
2015-04-17 [ USB ] R11 moved
2015-04-20 [ USB ] UART connection
2015-04-20 [ uSD ] Fiducials
2015-04-20 [ USB ] Fiducials; panel direction
2015-04-20 [ USB ][ SCH ] test pads are connected
2015-04-22 [ USB ] fix broken schematic link
2015-04-23 [ USB ] IC2, pin3 trace
2015-04-23 [ USB ] C2, Q1, Silk
2015-05-01 [ USB ] layer and silk fix
2015-05-03 [ USB ] LED1 description
2015-05-03 [ NEW ] MurataBLE_P
2015-05-03 [ USB_P ] Gerbers
2015-05-08 [ USB ] milling fix; mylib also
2015-05-12 [ USB_P ] send to manufactureing Eurocircuits.com
2015-07-01 [ uSD ][ SCH ] added RESET node
2015-07-22 [ FIX ] library update; add debug connector
2015-07-23 [ FIX ] fiducial; v-cut is 0.8mm width
2015-07-23 [ USB ][ SCH ] replace fiducial from 0.8mm to 2.0mm phi
2015-08-06 [ USB ] shorter milling; R6 and IC1 silk move
2015-08-06 [ uSD ] add 'Open Source Hardware' silk
2015-08-07 [ uSD ] uSD pin 8 is replaced to Vpp
2015-08-07 [ USB ] QFN33 paste mask change from library
2015-08-07 [ uSD ] panelise as r3
2015-08-10 [ uSD ][ USB ] library update
2015-08-10 [ NEW ][ SCH ][ BRD ] MurataMicroMB
2015-08-12 [ FIX ] add SPI ROM; board size extend; silk move
2015-08-12 [ SD ] update library
2015-08-13 [ uSD ] move silk; tiny trace fix
2015-08-13 [ uSD ] debug connector moved; increase panel size
2015-08-14 [ uSD ] OSHW icon replaced from library
2015-08-17 [uSD][SCH] P0_4/P0_5 function name slight change
    P0_4/TXD->/MOSI
    P0_5/RXD<-/SCK
2015-08-18 [ uSD ][ BRD ] CR_2125/R_1608_PADPAD update
2015-08-18 [ FIX ] add DCDC converter(for Vpp), microSD sockets, switches, USB circuit
2015-08-18 [ MB ][ SCH ] R/C/L values
2015-08-19 [ MB ] add OSHW icon
2015-08-19 [ uSD ] panelised as r3
2015-08-29 [ USB ] V-CUT marks
2015-08-29 [ MB ][ SCH ] connection to uSD sockets changed
2015-09-07 [ MB ] switches moved
2015-09-07 [ uSD ] wider milling
2015-09-07 [ USB ] extend milling move v-cut 1mm north
2015-09-07 [ uSD ] RCL value
2015-09-07 [ MB ] RCL value and size
2015-09-08 [ NEW ] MurataBLE_FS: BLE module,debugger,microSD and VPP generator on board
2015-09-16 [ MB ] add LED1/R13/R14
2015-09-16 [ FS ] add LED1/R13/R14
2015-09-18 [ FS ] silk move
2015-09-18 [ MB ][ SCH ] values and details change
2015-10-07 [ MB ] add R15/R16 function vs. pin number list
2015-10-07 [MB] L1 and IC1
2015-10-22 [ MB ][ SCH ] R3/4 to use digikey number
2015-10-27 [ MB ] layers fix
2015-10-28 [ NEW ] A14580_QFN40_0v5_P
2015-10-31 [ NEW ] DA14580_QFN40_0v5.sch/.brd rename from _P to let _P indicate panelled version
2015-10-31 [ FIX ][ 58X ] update schematic with library
2015-10-31 [ NEW ][ 58X ] Gerber fies and a gerbv project file
2015-11-09 [ MB ] resize R2 and C7
2015-11-09 ignores local zip archives
2015-11-10 [ MB ] R5/6/15/16 moved; add DETECT1/2 pin on schematic
2015-11-10 [ MB ] add R17-19
2015-11-10 [ MB ] add R20/21; R7/8/9 move
2015-11-10 [ MB ] move SW1-3, BL shares IC1 with nSRST
2015-11-10 [ MB ] pin1 to be used by TGT_RST; BL=P0_14
2015-11-10 [ MB ] move R7-9/15/16//20,C2,SW1-3; pinout list, library update
2015-11-12 [ FS ] TP1/2; library update
2015-11-14 [ MB ] library replace to dp_pcb_local; library update CON1/2/4
2015-11-14 [ FS ] library update CON2/4; pin connection shift to avoid SWD pins
2015-11-14 [ 58x ] add fiducial; increase sub board width; move whole board by 1mm North-East; add some value to parts
2015-11-16 [ uSD ] library update
2015-11-16 [ MB ] library update
2015-11-16 [ FS ] library update
2015-11-16 [ USB ] library update
2015-11-16 [ 58x ] library update
2015-11-16 tCream layer update as library
2015-11-17 [ 58x ] panelize and process gerber
2015-11-26 update eagle version: 7.5.0; library update
2015-11-26 update eagle version = 7.5.0; library update
2015-12-01 [ 58x ] IC1 - tCream; add a selecter (580 or 583)
2015-12-01 [ NEW ] DA14580_QFN40_0v5.md
2015-12-01 [58x] Gerber out; BOM update
2015-12-01 library update
2015-12-02 [ SD ] library update; add SWD connector; add Flash;
2015-12-03 [ SD ] disconnect VPP; SPI uses P0_4 to P0_7
2015-12-03 [ MB ] TP1,2,6,7 changed to use test pin; related Rs movee
2015-12-04 [ MB ] Fiducials renamed; moved TPs
2015-12-06 [ MB ] update package of LED1; add TP_4020; update package of IC2
2015-12-07 ignore *.lck
2015-12-16 [ 58x ] Q1 Digikey number replace
    728-1076-1-ND -> 1253-1342-1-ND
2015-12-23 [ MB ] TP12;IC4;CON2
2015-12-23 [ uSD ] TP1
2015-12-23 [ SD ]
2015-12-23 [ MB ]
2015-12-23 [ 58x ] v0.5 frozen
2015-12-23 [ 58x ] fork as previous version contains version number, but keep previous one
2015-12-29 [ 58x ] font alignment
2015-12-29 [ MB ] font alignment(by library)
2015-12-29 [ 58x ] BOM list titled
2015-12-29 [ NEW ][ MB ] BOM list markdown file
2016-02-23 IC4 replace package; TR1 and related moves
2016-02-24 MB and uSD
2016-03-02 [ MB ] Board and Sch are consistent
2016-03-02 [ USB ] add IC4/5
    replace IC2 symbol; change R11 connection
2016-03-02 [ USB ] SWSPI connections
2016-03-02 [ USB ] LED connection; SWD connection removed from 11U35
2016-03-02 [ USB ] r0.4
2016-03-03 [ USB ] no more 580.P1_x use for SPI
2016-03-03 [ USB ] OSHW; milling; CON1;
2016-03-03 [ USB ] move TR1, R10, IC1
2016-03-04 [ USB ] library CON1 update; Q1 replace; traces;
2016-03-04 [ USB ] add C13; R1/6 silk
2016-03-04 [ USB ] IC4 and 5 move
2016-03-04 [ USB ] IC2/Q1 silk
2016-03-04 [ USB ] IC4 and 5; traces
2016-03-04 [ USB ] traces
    TODO: SW1-3 library to update to have cream layer
2016-03-04 [ USB ] fix DRC error
2016-03-04 [ USB ] fix unnecessary foldings
2016-03-08 library update; add R12-13(shorted 1005 resistors)
2016-03-08 IC3 replace by IC_TTL_7400_SINGLE
2016-03-08 ignore eagle backup files
2016-03-08 [ MB ] IC2 and related fix; library update
2016-03-08 [ MB ] library update; IC2 trace
2016-03-08 [ USB ] short register
2016-03-10 [ USB ] P0_13/14 to be SWD pins
2016-03-10 [ USB ] library update; add X2; move R4/5/11; move LED1
    move revision mark silk
    move name metal
    X1 <> X2 25.4mm distance
2016-03-10 [ USB ] get narrower PCB width; CON1 and U1 at center of PCB 31->29mm width dummy header X2
2016-03-11 [ USB ] straight traces to BLE pad
2016-03-11 ignore lock files
2016-03-11 move csv and md into doc/ directory
2016-03-11 move images to images/
2016-03-11 BOM update
2016-03-11 [USB] top/bottom coordinates
2016-03-11 [ USB ] add SWD pulp R14/15
2016-03-11 [ MB ] library update; update values; BOM update
2016-03-15 [ USB ]add values; panelized
2016-03-15 [ USB ] GERBER r0.4
2016-03-15 [ USB ] BOM and placement
2016-03-16 [ USB ] fix OpenDrain problem
    P0_4 and 5 are used for I2C; has limitation of open drain
    change polarity of LED1 to pull current from 3.3V line
2016-03-16 [ USB ] add LED2, R16-18
    UART TX/RX LEDs and blinky a LED combined to LED2
2016-03-16 [ USB ] IC1 replace and necessary moves
2016-03-19 [ USB ] trace
2016-05-15 [ USB ] add 3.3V pin; silk; move R4/5/11
2016-05-15 [ USB ] IC1 has value
2016-05-15 [ USB ] GERBER as per aef7891
2016-05-15 [ USB ] BOM
2016-05-15 [ MB ] update library
2016-05-15 [ USB ] stencil Gerber layer
2016-06-11 [ USB ] gerbv file
2016-06-30 [ r0.4 ] update library
    typo fix: P0_32 -> P0_23;
    add 11U35 PinNames for SPI flash
2016-09-03 ignore .DS_Store
2016-09-03 [ NEW ] add da14580sdk as submodule
2016-10-24 submodule (sdk) update
2017-07-26 add sensor9dof pcb project as submodule
2017-07-30 update senso9dof submodule
2017-07-30 r0.5 started
2017-07-30 replace IC2/3 to smaller outlined devices
